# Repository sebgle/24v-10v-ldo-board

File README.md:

# 24 V → 10 V LDO Regulator Board

A small two-layer linear regulator board that takes a 24 V input on a screw terminal and delivers a fixed 10 V output on a second screw terminal. Built in KiCad 8, fabricated, and hand-assembled during my sophomore year for Texas Guadaloop at UT Austin.

The point of the project was to carry one board through the entire hardware flow: part selection from a manufacturer datasheet, schematic capture, custom symbol and footprint creation, layout, design review with more experienced peers, gerber export, fabrication, assembly, and bring-up, rather than to build something complex. 

This board was used for powering the hyperloop pod's safety lights.

---

## Board at a glance

| | |
|---|---|
| Input | 24 V, 2-pin screw terminal |
| Output | 10 V, 2-pin screw terminal |
| Regulator | Nisshinbo Micro Devices **R1501** series LDO, TO-252-5 |
| Layers | 2 (F.Cu, B.Cu) |
| Board size | 44.04 × 19.04 mm |
| Board thickness | 1.6 mm |
| Vias | 4 |
| Mounting | 4 × 2.2 mm corner holes |
| Routing | Copper pours for +24 V and GND; 0.2 mm traces for +10 V |

---

## Why the R1501

I needed a regulator that could survive a 24 V rail and still source a useful amount of current at 10 V. The [Nisshinbo R1501 series](https://www.nisshinbo-microdevices.co.jp/en/products/ldo-linear-regulator/spec/?product=r1501) fit:

- Input range covering 24 V
- Output voltage available at 10 V
- 1 A class output current
- Built-in thermal shutdown, current limiting, and short-circuit protection
- Available in TO-252-5 (DPAK), a surface-mount package with a large thermal tab I could hand-solder

KiCad had no symbol or footprint for this part, so I drew the symbol myself into a personal library (`sebastian_library`) straight from the datasheet pinout and used the stock `Package_TO_SOT_SMD:TO-252-5_TabPin3` footprint.

---

## Two things peers taught me

### 1. Copper pours instead of traces

My first layout routed the input and output rails as ordinary traces. A teammate with more layout experience pointed out that for a power board this is the wrong instinct: a trace has to be sized for its current, and a thin one both drops voltage and heats up. 

The final layout uses on pours instead:

- **F.Cu** carries a `+24V` zone covering the input half of the board
- **B.Cu** carries a `GND` zone covering the whole board

This also gave the regulator's thermal tab a large copper area to dump heat into, which is what a linear regulator dropping 14 V actually needs.

What I did **not** do, and should have, is extend the same reasoning to the output. The `+10V` net is still routed the old way: four 0.2 mm segments running from the regulator's Vout pin past the output capacitor to the terminal.

The red region is the +24 V pour on the front layer; the blue is the ground pour on the back.

### 2. Why the IC needs capacitors right next to its pins

I originally understood decoupling capacitors as "something you put on a power rail." What I did not understand was that where you put them is the entire point.

The explanation that made it click: the loop between the capacitor and the IC pin has inductance, and inductance is what resists a sudden change in current. When the regulator's load steps, the current has to come from somewhere immediately, faster than the 24 V supply and its wiring can respond. A capacitor a few millimetres from the pin can supply that current through a tiny loop. 

For an LDO specifically there is a second reason: the output capacitor is part of the regulator's feedback loop. The control loop's stability depends on its capacitance and its ESR, which is why datasheets specify a range rather than a minimum.

So the layout places C2 (input) directly adjacent to the Vdd pin and C1 (output) directly adjacent to Vout, both with the shortest possible return path into the ground pour underneath.

---

## What I would do differently

- **The output rail is under-coppered.** The `+24V` input has a pour behind it; the `+10V` output is carried by 0.2 mm traces alone. A 0.2 mm trace in 1 oz copper is nowhere near sized for a regulator rated in the amps, so the output rail is what actually limits safe load current on this board. Pouring the output half of F.Cu as a `+10V` zone would have been the same edit I already made on the input side.
- **No thermal analysis.** I never calculated the actual junction temperature at a given load current. A 24 V → 10 V linear drop is 58% of the input power turned into heat, and the safe operating current is set by the copper area.

Luckily, none of these stopped the board from working! But it would be nice if I needed to redo it.

---

---

*Sophomore-year personal project, ECE @ UT Austin. Designed in KiCad 8, fabricated externally, hand-assembled and bench-verified.*

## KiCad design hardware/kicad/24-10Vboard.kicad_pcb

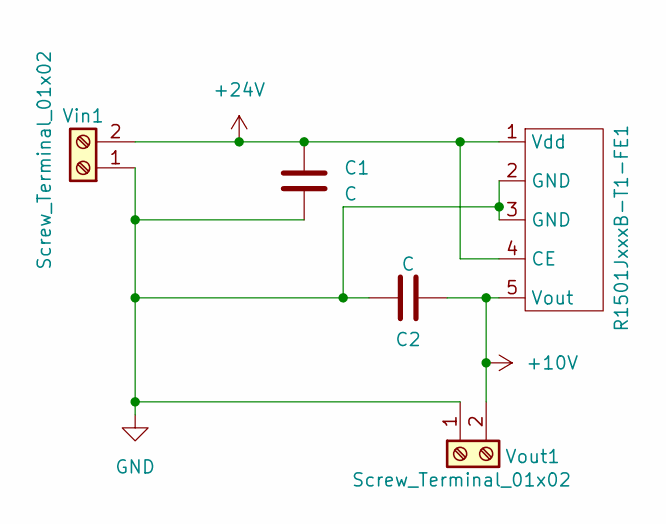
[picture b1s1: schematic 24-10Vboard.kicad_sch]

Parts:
C1: C; C_Radial_D5.0mm_H11.0mm_P2.00mm
C2: C; C_Radial_D6.3mm_H11.0mm_P2.50mm
R1501JxxxB-T1-FE1: TO-252-5_TabPin3
Vin1: Screw_Terminal_01x02; Screw_Terminal_2P
Vout1: Screw_Terminal_01x02; Screw_Terminal_2P

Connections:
+10V: C2.2, R1501JxxxB-T1-FE1.5 (Vout), Vout1.2
+24V: C1.2, R1501JxxxB-T1-FE1.1 (Vdd), R1501JxxxB-T1-FE1.4 (CE), Vin1.2
GND: C1.1, C2.1, R1501JxxxB-T1-FE1.2 (GND), R1501JxxxB-T1-FE1.3 (GND), Vin1.1, Vout1.1

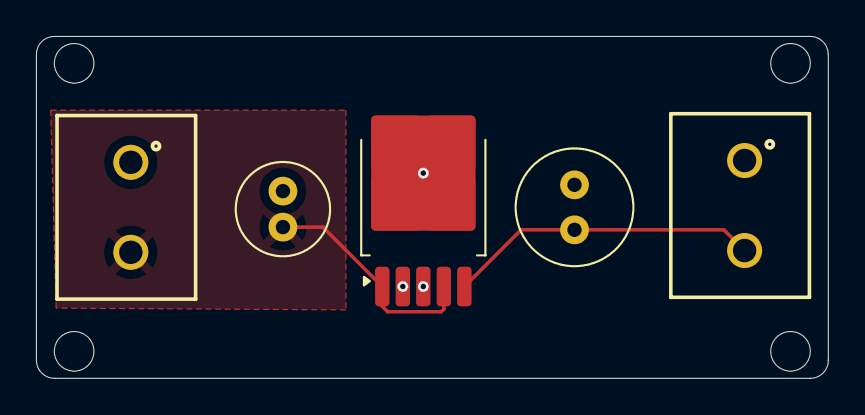
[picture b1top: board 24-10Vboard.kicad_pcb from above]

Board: 2 copper layers, 44.0 x 19.0 mm, 5 parts (0 on the bottom side), 3 nets.
